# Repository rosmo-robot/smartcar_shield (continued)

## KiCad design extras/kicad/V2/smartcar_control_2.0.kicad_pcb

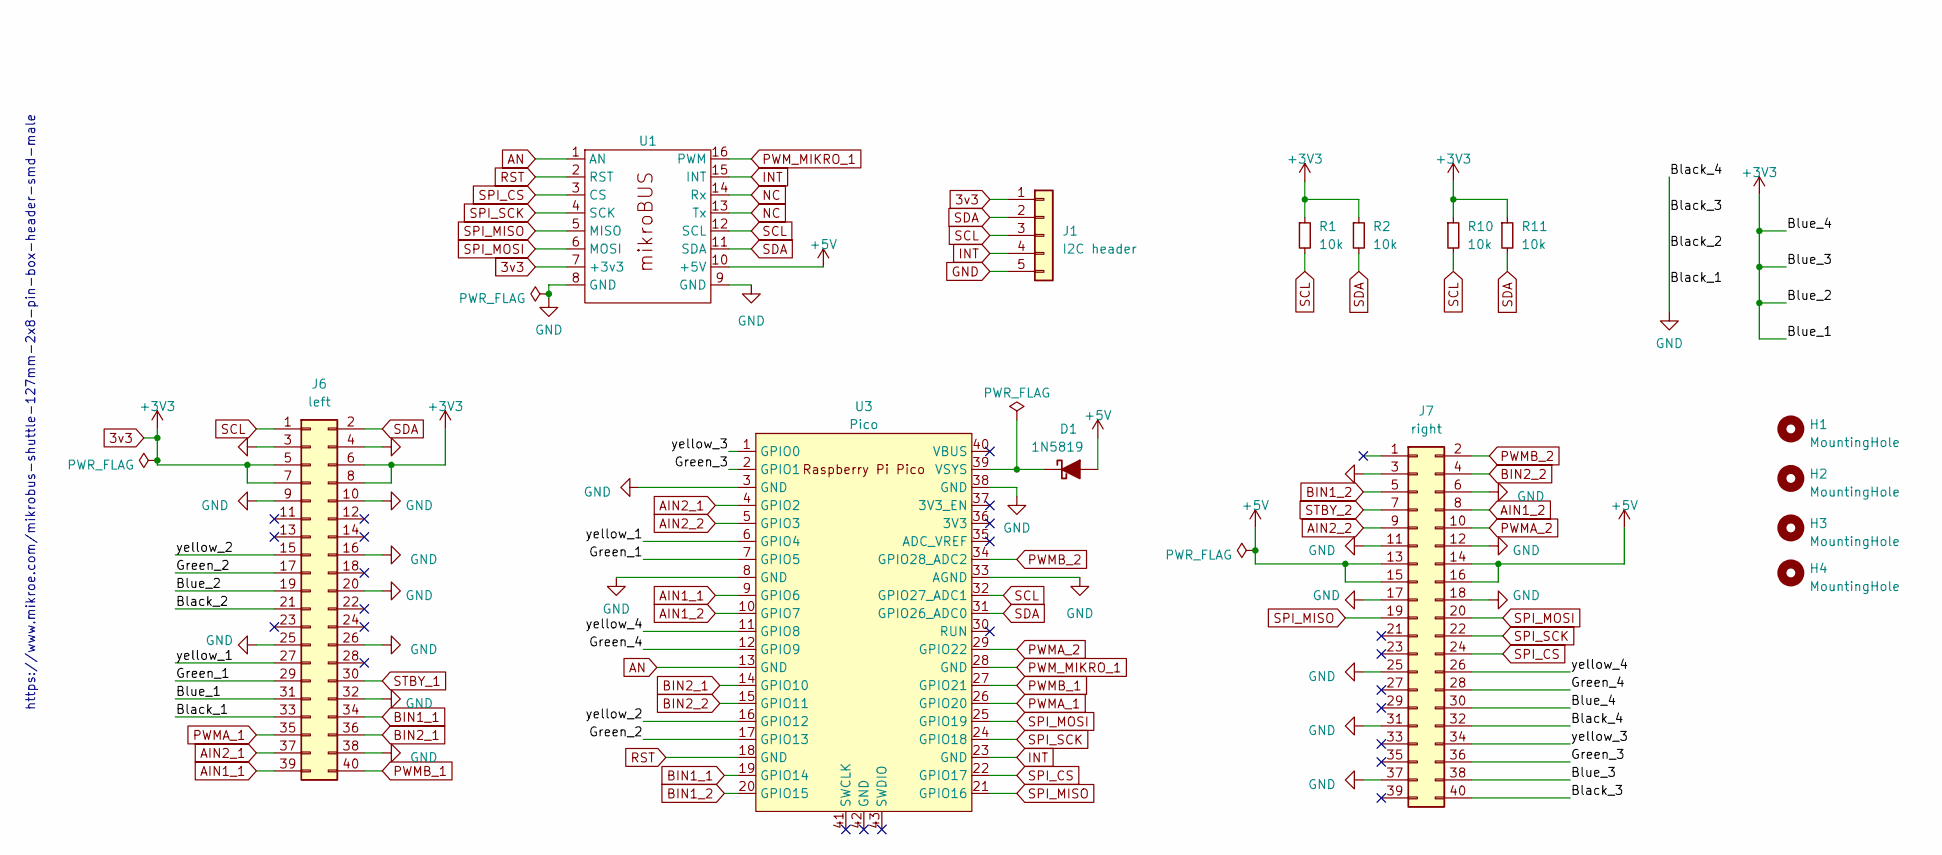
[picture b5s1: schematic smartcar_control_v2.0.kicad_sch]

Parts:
D1: 1N5819; D_DO-41_SOD81_P7.62mm_Horizontal; LCSC C698893
H1, H2, H3, H4: MountingHole; MountingHole_3.2mm_M3
J1: I2C header; PinHeader_1x05_P2.54mm_Vertical
J6: left; PinHeader_2x20_P2.54mm_Vertical
J7: right; PinHeader_2x20_P2.54mm_Vertical
R1, R2: 10k; R_Axial_DIN0207_L6.3mm_D2.5mm_P7.62mm_Horizontal
R10, R11: 10k; R_0603_1608Metric; LCSC C25804
U1: mikroBUS
U3: Pico; RPi_Pico_SMD_TH

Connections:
3v3: J1.1, J6.5, J6.6, J6.7, J6.8, J6.19, J6.31, J7.30, J7.38, R1.1, R2.1, R10.1, R11.1, U1.7 (+3v3)
+5V: D1.2 (A), J7.13, J7.14, J7.15, J7.16, U1.10 (+5V)
/Green_1: J6.29, U3.7 (GPIO5)
/Green_2: J6.17, U3.17 (GPIO13)
/Green_3: J7.36, U3.2 (GPIO1)
/Green_4: J7.28, U3.12 (GPIO9)
/yellow_1: J6.27, U3.6 (GPIO4)
/yellow_2: J6.15, U3.16 (GPIO12)
/yellow_3: J7.34, U3.1 (GPIO0)
/yellow_4: J7.26, U3.11 (GPIO8)
AIN1_1: J6.39, U3.9 (GPIO6)
AIN1_2: J7.8, U3.10 (GPIO7)
AIN2_1: J6.37, U3.4 (GPIO2)
AIN2_2: J7.9, U3.5 (GPIO3)
AN: U1.1 (AN), U3.13 (GND)
BIN1_1: J6.34, U3.19 (GPIO14)
BIN1_2: J7.5, U3.20 (GPIO15)
BIN2_1: J6.36, U3.14 (GPIO10)
BIN2_2: J7.4, U3.15 (GPIO11)
GND: J1.5, J6.3, J6.4, J6.9, J6.10, J6.16, J6.20, J6.21, J6.25, J6.26, J6.32, J6.33, J6.38, J7.3, J7.6, J7.11, J7.12, J7.17, J7.18, J7.25, J7.31, J7.32, J7.37, J7.40, U1.8 (GND), U1.9 (GND), U3.3 (GND), U3.8 (GND), U3.33 (AGND), U3.38 (GND)
INT: J1.4, U1.15 (INT), U3.23 (GND)
NC: U1.13 (Tx), U1.14 (Rx)
unnamed: D1.1 (K), U3.39 (VSYS)
PWMA_1: J6.35, U3.26 (GPIO20)
PWMA_2: J7.10, U3.29 (GPIO22)
PWMB_1: J6.40, U3.27 (GPIO21)
PWMB_2: J7.2, U3.34 (GPIO28_ADC2)
PWM_MIKRO_1: U1.16 (PWM), U3.28 (GND)
RST: U1.2 (RST), U3.18 (GND)
SCL: J1.3, J6.1, R1.2, R10.2, U1.12 (SCL), U3.32 (GPIO27_ADC1)
SDA: J1.2, J6.2, R2.2, R11.2, U1.11 (SDA), U3.31 (GPIO26_ADC0)
SPI_CS: J7.24, U1.3 (CS), U3.22 (GPIO17)
SPI_MISO: J7.19, U1.5 (MISO), U3.21 (GPIO16)
SPI_MOSI: J7.20, U1.6 (MOSI), U3.25 (GPIO19)
SPI_SCK: J7.22, U1.4 (SCK), U3.24 (GPIO18)
STBY_1: J6.30
STBY_2: J7.7

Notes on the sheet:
https://www.mikroe.com/mikrobus-shuttle-127mm-2x8-pin-box-header-smd-male

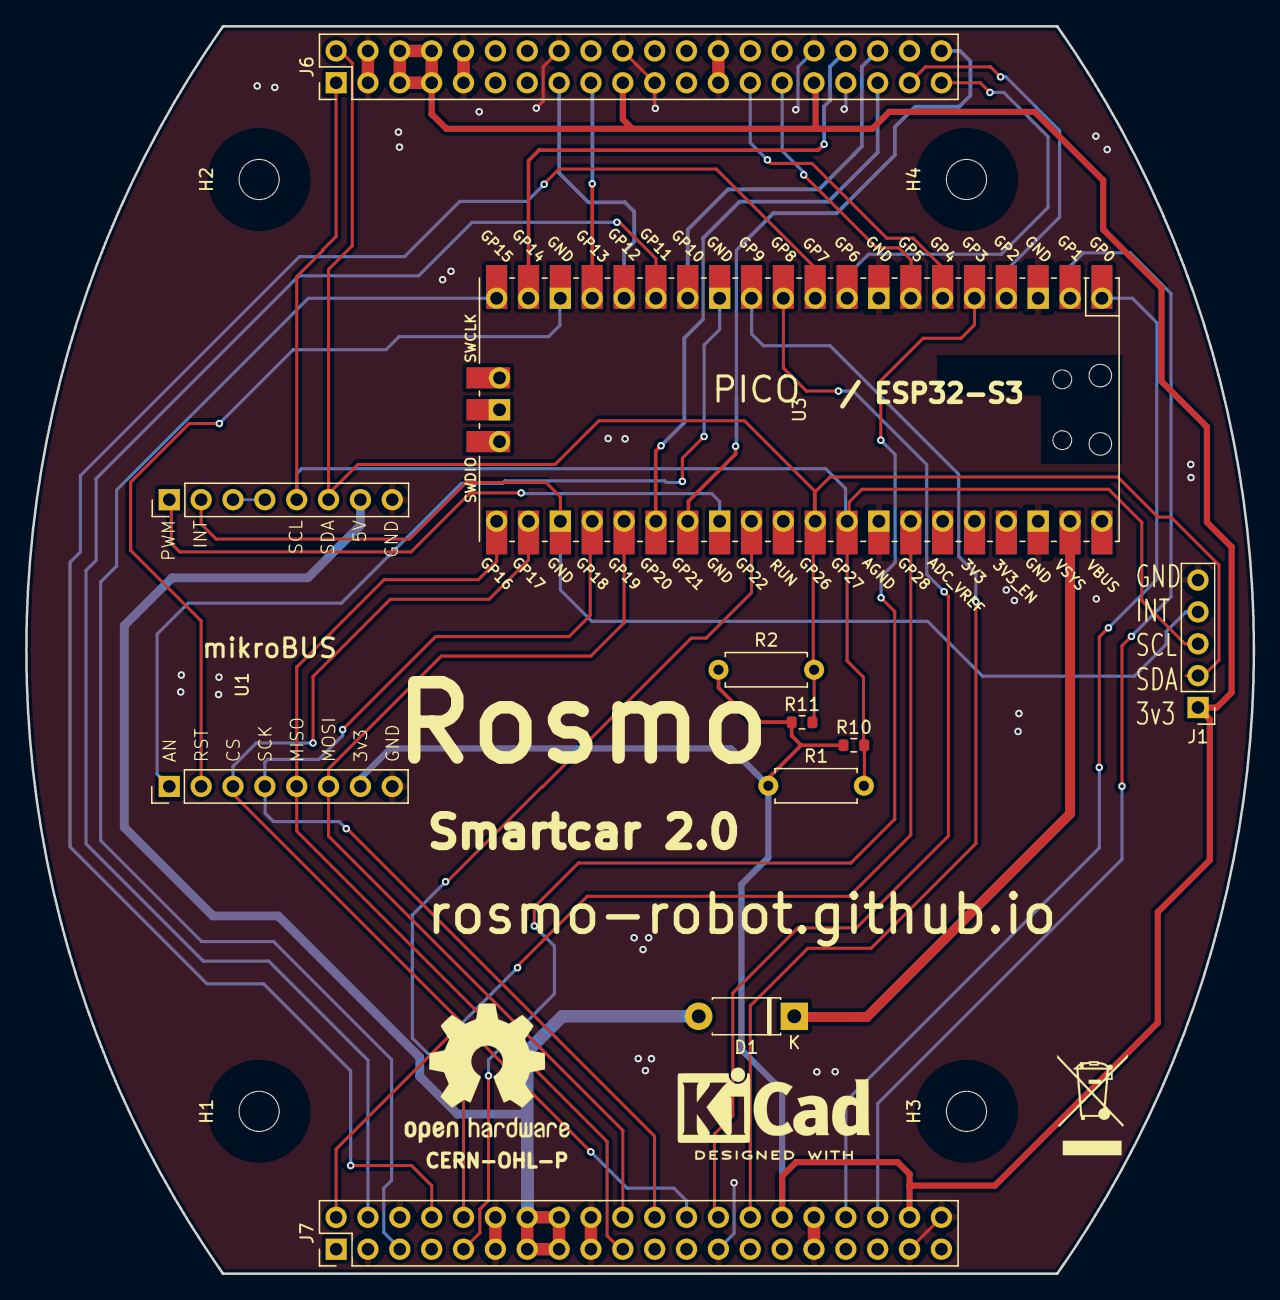
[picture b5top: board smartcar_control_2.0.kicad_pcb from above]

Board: 2 copper layers, 97.9 x 99.4 mm, 17 parts (0 on the bottom side), 35 nets.

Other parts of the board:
FID2: Fiducial; WEEE-Logo_5.6x8mm_SilkScreen
FID3: Fiducial; OSHW-Logo2_14.6x12mm_SilkScreen
FID4: Fiducial; KiCad-Logo2_6mm_SilkScreen

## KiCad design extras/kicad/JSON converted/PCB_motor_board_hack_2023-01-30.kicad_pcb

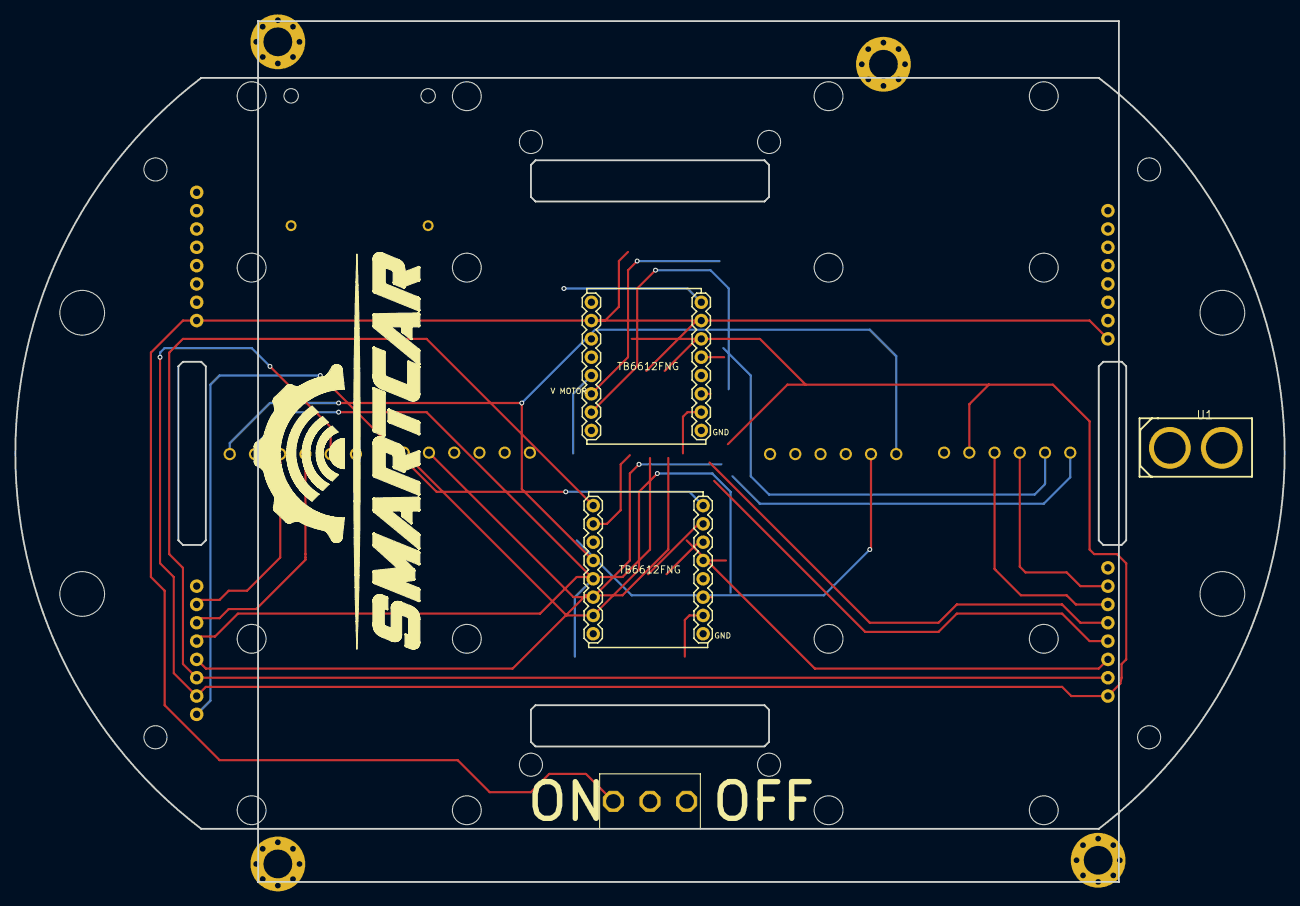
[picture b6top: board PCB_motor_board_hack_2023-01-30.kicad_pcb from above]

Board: 2 copper layers, 176.0 x 119.4 mm, 25 parts (0 on the bottom side), 18 nets.

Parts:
1: NANO-ITX_120X120
J1, J2, J3, J4: 1X08_NO_SILK
J5, J6, J7, J8: 1X08
LOGO1, LOGO2: OSHW-LOGOL; OSHW-LOGO-L
MOTOR2, MOTOR3, MOTOR4, MOTOR5: SMARTCAR_MOTOR; SMARTCAR_MOTOR_MOUNT_HOLES
SMRTCR1: SMARTCAR_LOGOMEDIUM; SMARTCAR_LOGO_MEDIUM
SW1: SPDT-HIGH-AMP-SWITCHPTH; SPDT-0.2-THICK-PINS
U1: CONN-TH_XT60
U8: POLULUMOTORBRACKETPPCB
U$1, U$2: BUMPER_020522_SCREWS; BUMPER_2_SCREWS_NARROW
X1, X2, X3, X4: 6; 1751280

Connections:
BAT_GND: J1.1, J3.1, SW1.POS1
EN_L_1: J2.7, X1.4
EN_L_2: J2.6, X1.3
EN_R_1: J4.7, X3.4
EN_R_2: J4.6, X3.3
GND: J2.8, J4.8, J5.3, J5.8, J6.1, J7.1, J8.3, J8.8, SW1.SIG, X1.1, X3.1
MOTOR_L_EN: J2.1, J6.8, J7.8
MOTOR_L_IN1: J2.4, J6.6, J7.6
MOTOR_L_IN2: J2.5, J6.7, J7.7
MOTOR_L_OUT1: J5.4, J8.4, X1.6, X4.1
MOTOR_L_OUT2: J5.5, J8.5, X1.5, X4.2
MOTOR_R_EN: J4.3, J6.2, J7.2
MOTOR_R_IN1: J4.5, J6.4, J7.4
MOTOR_R_IN2: J4.4, J6.3, J7.3
MOTOR_R_OUT1: J5.7, J8.7, X2.1, X3.6
MOTOR_R_OUT2: J5.6, J8.6, X2.2, X3.5
MOTOR_VCC: J2.3, J4.2, J5.1, J8.1
VCC: J2.2, J4.1, J5.2, J6.5, J7.5, J8.2, X1.2, X3.2

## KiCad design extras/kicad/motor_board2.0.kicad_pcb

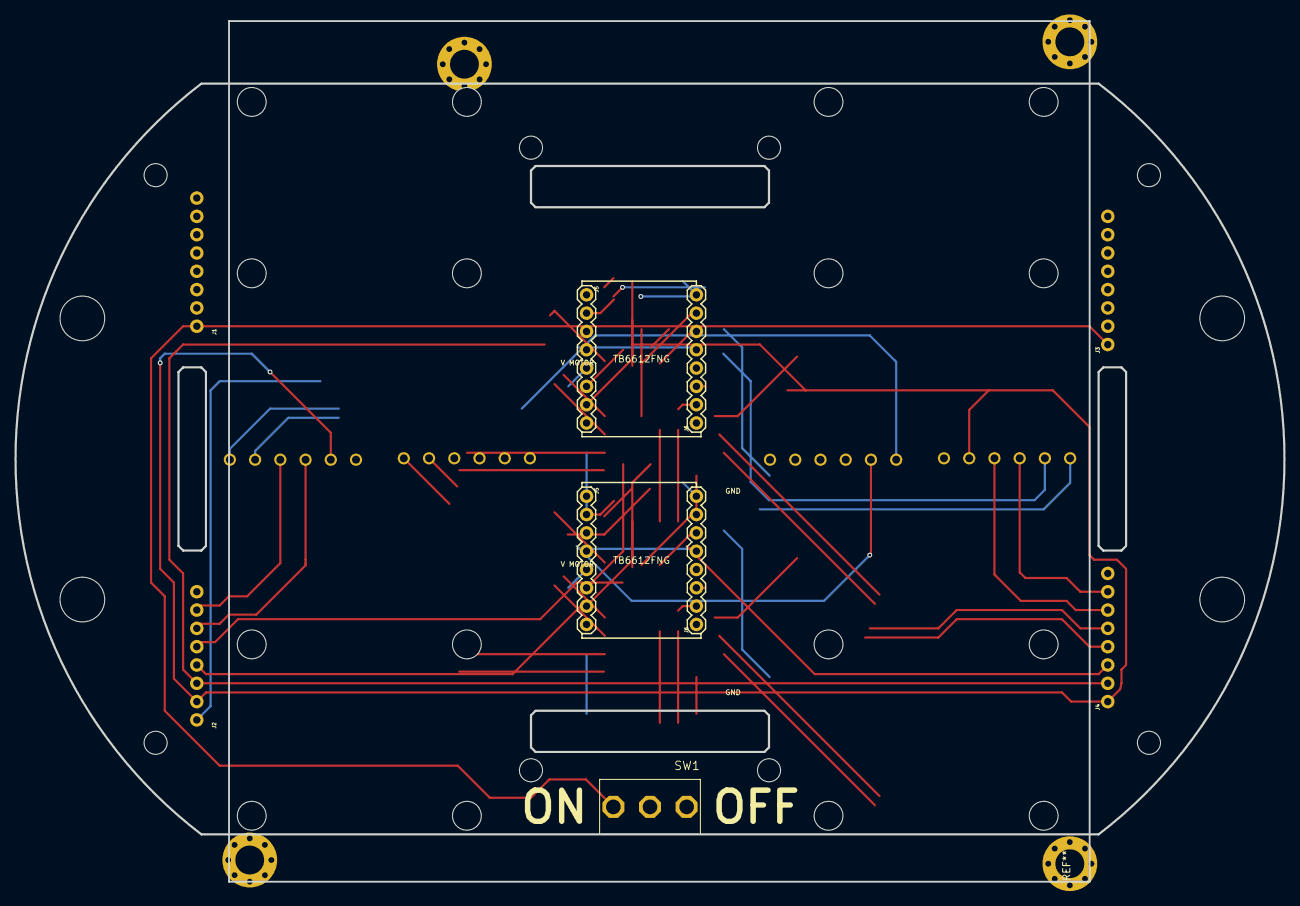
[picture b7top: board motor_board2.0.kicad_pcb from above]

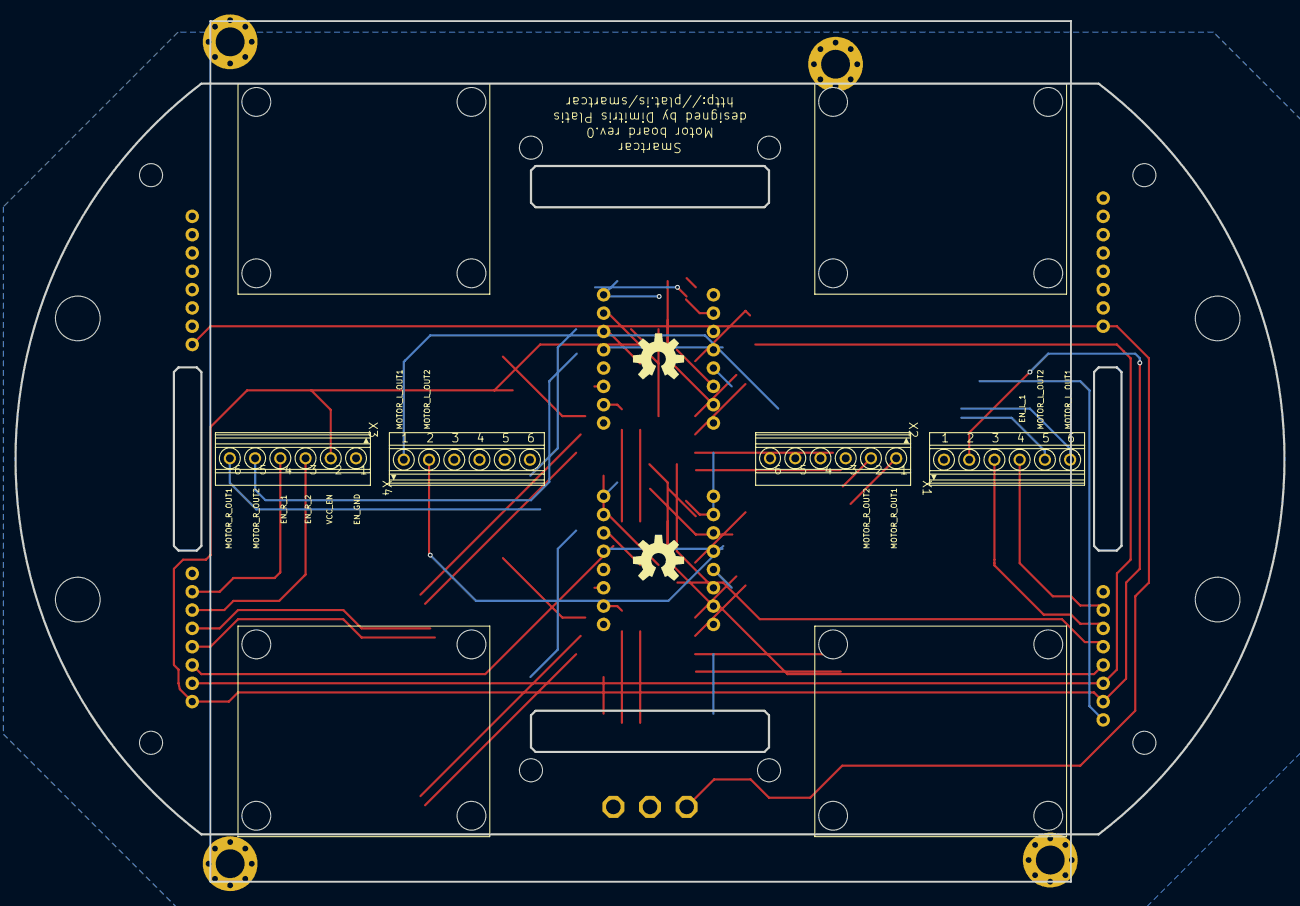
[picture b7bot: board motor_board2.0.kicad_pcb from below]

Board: 2 copper layers, 176.0 x 119.4 mm, 29 parts (10 on the bottom side), 18 nets.

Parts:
@HOLE0, @HOLE1, @HOLE2, @HOLE3, @HOLE4, @HOLE5, @HOLE6, @HOLE7: (no value)
J1, J2, J3, J4: 1X08_NO_SILK
J5, J5#2, J6, J6#2: 1X08
LOGO1, LOGO1#2: OSHW-LOGOL; OSHW-LOGO-L
MOTOR2, MOTOR3, MOTOR4, MOTOR5: SMARTCAR_MOTOR; SMARTCAR_MOTOR_MOUNT_HOLES
SW1: SPDT-HIGH-AMP-SWITCHPTH; SPDT-0.2-THICK-PINS
U$1, U$2: BUMPER_020522_SCREWS; BUMPER_2_SCREWS_NARROW
X1, X2, X3, X4: 1751280

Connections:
BAT_GND: J1.1, J3.1, SW1.POS1
EN_L_1: J2.7, X1.4
EN_L_2: J2.6, X1.3
EN_R_1: J4.7, X3.4
EN_R_2: J4.6, X3.3
GND: J2.8, J4.8, J5.3, J5.8, J5#2.3, J5#2.8, J6.1, J6#2.1, SW1.SIG, X1.1, X3.1
MOTOR_L_EN: J2.1, J6.8, J6#2.8
MOTOR_L_IN1: J2.4, J6.6, J6#2.6
MOTOR_L_IN2: J2.5, J6.7, J6#2.7
MOTOR_L_OUT1: J5.4, J5#2.4, X1.6, X4.1
MOTOR_L_OUT2: J5.5, J5#2.5, X1.5, X4.2
MOTOR_R_EN: J4.3, J6.2, J6#2.2
MOTOR_R_IN1: J4.5, J6.4, J6#2.4
MOTOR_R_IN2: J4.4, J6.3, J6#2.3
MOTOR_R_OUT1: J5.7, J5#2.7, X2.1, X3.6
MOTOR_R_OUT2: J5.6, J5#2.6, X2.2, X3.5
MOTOR_VCC: J2.3, J4.2, J5.1, J5#2.1
VCC: J2.2, J4.1, J5.2, J5#2.2, J6.5, J6#2.5, X1.2, X3.2

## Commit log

2023-01-28 Incomplete draft
2023-01-28 Just outlines routing not done
2023-01-28 Incomplete
2023-01-29 test1
2023-01-30 Add BNO-85
2023-01-31 Upload Waffle plates from Turtlebot3
    https://www.turtlebot.com/turtlebot3/
2023-02-02 Messy schematic - Includes components
    Incomplete schematic that shows all the components on the Control/Modules board
2023-02-09 Schematic
2023-02-11 Version With Silkscreen
    Added here so as to not conflict with the /v2 folder
2023-02-21 Update BOM-Power.csv
    Added some LCSC part numbers
2023-02-26 BNO085 footprint
2023-02-26 BNO85 footprint and schematic
2023-02-27 added 2242 footprint
2023-02-28 BLDC version
2023-02-28 Added UEXT, Mikroe & 7Pin SPI
    (7pin SPI is break out garden) so we don't forget them
2023-02-28 Added links to parts
2023-03-03 test
2023-03-03 Minor schematic change
    t
2023-03-04 Added control-sam
    A
2023-03-04 Added larger M.2 & Mikro click board footprints
2023-03-08 Add stp for SBC
2023-03-09 BNO85.stp
2023-03-09 Image update
2023-03-11 Draft of schematic - needs tidying
2023-03-13 Initial gh-pages commit
2023-03-13 Deploying to gh-pages from @ b442313a1caf6a2233043ee700ad081950432807 🚀
2023-03-20 Idea for Mikro
    Rough PCB & Schematic
2023-03-26 Deploying to gh-pages from @ c4728ef3a92b9360a59c805fa84a3aaec3fbbaeb 🚀
2023-03-26 Deploying to gh-pages from @ d3c1b3400f5858562b2f8bc383858f53273120b1 🚀
2023-03-26 Deploying to gh-pages from @ 5cce0cfc93f92c7ea4b3ffaf167d120bba5fe8dc 🚀
2023-03-27 Deploying to gh-pages from @ 5ce153ebbc52af464dadbbb6b91e68313588e84c 🚀
2023-04-11 Some changes to Mikro
2023-04-18 Updated sam-schematic
    Two Mikroe headers.
2023-05-13 Two Mikro
2023-05-18 Simplified a bit
    simplified
2023-05-18 Update README.md
    Added https://github.com/YuzukiHD/YuzukiChameleon
2023-05-19 Update ControlSam.kicad_sch
    Tidying
2023-05-20 Update
    Update
2023-05-20 Update ControlSam.kicad_sch
    Sync
2023-05-20 Footprint for vertical USB
    https://www.lcsc.com/product-detail/USB-Connectors_G-Switch-G-Switch-GT-USB-7038E_C2982477.html
2023-05-20 Vertical USB
    sync
2023-05-21 Added Qwiic
2023-08-13 Create pico-notes
2023-09-02 Pico version
